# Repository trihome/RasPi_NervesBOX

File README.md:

# Nerves BOX for Raspberry Pi

## はじめに

このボードは、産業用に使用される機器（例：24V駆動のスイッチ、センサー、リレーなど）をRaspberry Piへ接続できるようにします。

詳しくは、Qiitaの記事「[Elixir/NervesでPLC(多機能リレー)を作ってみた](https://qiita.com/myasu/private/a6664d3a3c76503affc7)」をご覧ください。

## 仕様

|機能|仕様|補足|
|:--|:--|:--|
|出力|4ch（フォトリレー絶縁）|シンク（NPN）・ソース（PNP）駆動切り替え可能。各chの動作確認LEDあり。|
|入力|4ch（フォトカプラ絶縁）|〃|
|AD変換|10bit 2ch|非絶縁・入力保護のダイオード付き|
|時刻保持|リアルタイムクロックDS1307|ボタン電池でバックアップ|
|GROVEコネクタ|あり、I2C x 1|5V電源タイプ|
|外部UART端子|あり x 1|RaspberryPiのUARTに直結|
|電源|5V系/24V系は個別に供給|それぞれポリスイッチ（過電流防止）あり|

**J5, J7の接続**

|対応表|GPIO（BCM表記）|本機の端子|
|:--|:--|:--|
|入力|12|X0|
|〃|16|X1|
|〃|20|X2|
|〃|21|X3|
|出力|6|Y0|
|〃|13|Y1|
|〃|19|Y2|
|〃|26|Y3|

**J2の接続**

|駆動したい方法|Pow24+In|Pow24-In||D16|D13||X側COM端子|Y側COM端子|
|:--|:--|:--|:--|:--|:--|:--|:--|:--|
|シンク|+24V|GND|→|点灯|消灯||GND|+24V|
|ソース|GND|+24V|→|消灯|点灯||+24V|GND|

## 作り方

[Manual](doc/README_pcb.jp.md)をご覧ください。

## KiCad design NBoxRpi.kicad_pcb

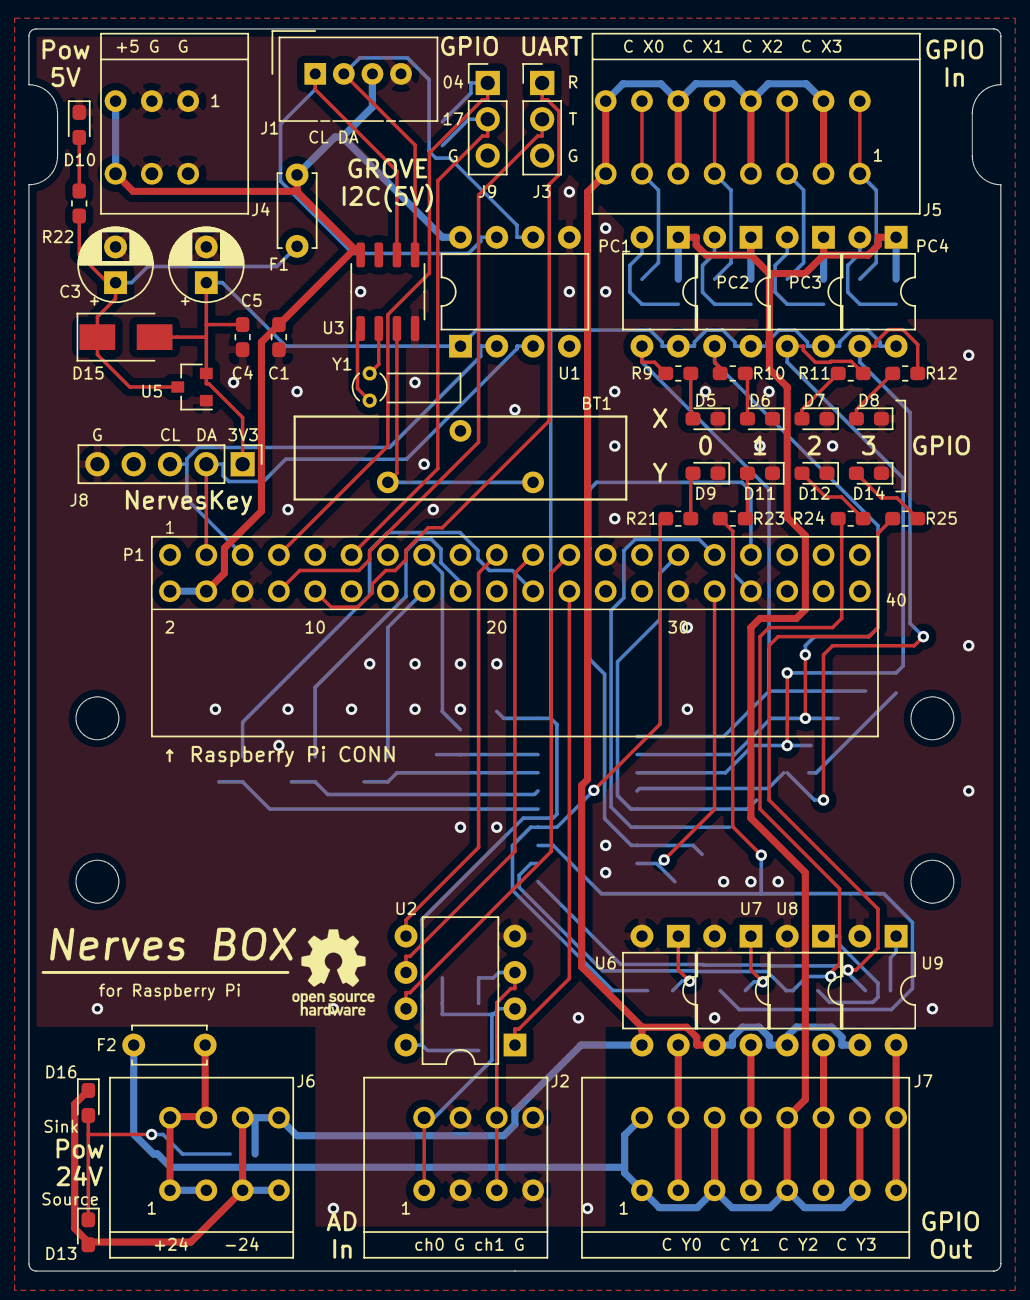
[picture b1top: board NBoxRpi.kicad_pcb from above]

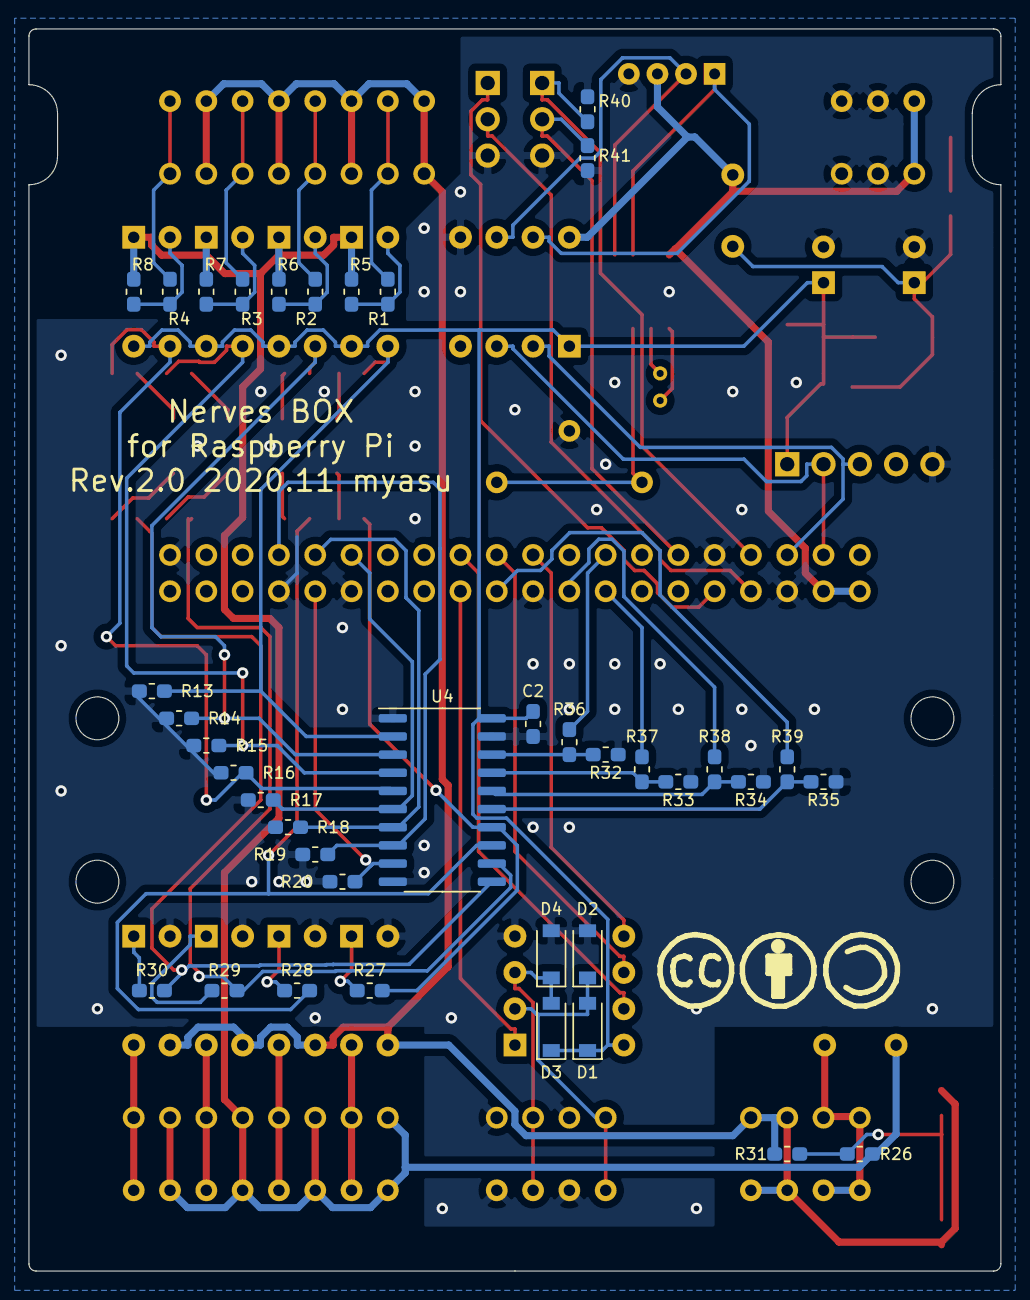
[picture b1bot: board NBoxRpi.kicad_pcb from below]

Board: 2 copper layers, 68.0 x 86.9 mm, 95 parts (38 on the bottom side), 70 nets.

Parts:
BT1: CH243-2032LF; BatteryHolder_Keystone_CH74-2032LF
C1, C2, C4: 0.1uF; C_0603_1608Metric_Pad1.05x0.95mm_HandSolder
C3: 100uF; CP_Radial_D5.0mm_P2.50mm
C5: 220uF; CP_Radial_D5.0mm_P2.50mm
D1, D2, D3, D4: 1N4148W; D_SOD-123
D5, D6, D7, D8: Gr; LED_0603_1608Metric_Pad1.05x0.95mm_HandSolder
D9, D11, D12, D14: Ye; LED_0603_1608Metric_Pad1.05x0.95mm_HandSolder
D10, D13, D16: Red; LED_0603_1608Metric_Pad1.05x0.95mm_HandSolder
D15: SBR1A40SA; D_SMA
F1: 0.17A(MAX0.34); C_Disc_D5.0mm_W2.5mm_P5.00mm
F2: 0.5A(MAX1A); C_Disc_D5.0mm_W2.5mm_P5.00mm
H1: MountingHole; OSHW-Logo_5.7x6mm_SilkScreen
H2: MountingHole; CC-BY-SA
J1: GROVE CONN; NS-Tech_Grove_1x04_P2mm_Vertical
J2, J6: TB401-1-4-E; Terminal_TB401-1-4-E
J3, J9: Pin Header 3; PinHeader_1x03_P2.54mm_Vertical
J4: TB401-1-3-E; Terminal_TB401-1-3-E
J5: TB401-1-8-E; Terminal_TB401-1-8-E
J7: TB401-1-3-E; Terminal_TB401-1-8-E
J8: Pin Header 4; PinHeader_1x05_P2.54mm_Vertical
MH1, MH2, MH3, MH4: MountingHole; MountingHole_3mm
P1: RasPi CONN; Connector_21602X20GRE
PC1, PC2, PC3, PC4: FOD814A300W; DIP-4_W7.62mm
R1, R2, R3, R4, R5, R6, R7, R8, R26, R31: 4.7k; R_0603_1608Metric_Pad1.05x0.95mm_HandSolder
R9, R10, R11, R12, R36, R37, R38, R39: 1k; R_0603_1608Metric_Pad1.05x0.95mm_HandSolder
R13, R14, R15, R16, R17, R18, R19, R20, R32, R33, R34, R35, R40, R41: 10k; R_0603_1608Metric_Pad1.05x0.95mm_HandSolder
R21, R23, R24, R25, R27, R28, R29, R30: 330; R_0603_1608Metric_Pad1.05x0.95mm_HandSolder
R22: 470; R_0603_1608Metric_Pad1.05x0.95mm_HandSolder
U1: AE-PCA9306; DIP-8_W7.62mm
U2: MCP3002; DIP-8_W7.62mm
U3: DS1307+; SO-8_3.9x4.9mm_P1.27mm
U4: 74HC541; SO-20_5.3x12.6mm_P1.27mm
U5: MCP1703AT-3302E; SOT-23
U6, U7, U8, U9: TLP222A; DIP-4_W7.62mm
Y1: 32.768kHz; Crystal_Round_D2.0mm_Vertical

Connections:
+3V3: C2.1, C4.1, C5.1, D1.1, D3.1, D15.2, J8.1, PC1.4, PC2.4, PC3.4, PC4.4, U1.1, U2.8, U4.20, U5.2
+5V: C1.1, F1.2, J1.3, J4.5, J4.6, P1.2, P1.4, U1.8, U3.8
/AD0: D1.2, D2.1, J2.1, J2.2, U2.2
/AD1: D3.2, D4.1, J2.5, J2.6, U2.3
/GPIO2(SDA1): J8.2, P1.3, U1.3
/GPIO3(SCL1): J8.3, P1.5, U1.2
/GPIO4(GCLK): J9.1, P1.7, R40.1
/GPIO5: P1.29, R17.1, U4.6
/GPIO6: P1.31, R18.1, U4.7
/GPIO8(SPI0_CE_N): P1.24, U2.1
/GPIO9(SPI0_MISO): P1.21, U2.6
/GPIO10(SPI0_MOSI): P1.19, U2.5
/GPIO11(SPI0_SCK): P1.23, U2.7
/GPIO12(PWM0): P1.32, R20.1, U4.9
/GPIO13(PWM1): P1.33, R19.1, U4.8
/GPIO14(TXD0): J3.2, P1.8
/GPIO15(RXD0): J3.1, P1.10
/GPIO17(GEN0): J9.2, P1.11, R41.1
/GPIO22(GEN3): P1.15, R36.1
/GPIO23(GEN4): P1.16, R37.1
/GPIO24(GEN5): P1.18, R38.1
/GPIO25(GEN6): P1.22, R39.1
/Pow24+: F2.1, J7.1, J7.2, J7.5, J7.6, J7.9, J7.10, J7.13, J7.14, PC1.1, PC2.1, PC3.1, PC4.1, R5.1, R6.1, R7.1, R8.1, R26.1
/Pow24+In: F2.2, J6.1, J6.2, J6.3, J6.4
/Pow24-: D13.2, D16.1, J5.3, J5.4, J5.7, J5.8, J5.11, J5.12, J5.15, J5.16, J6.5, J6.6, J6.7, J6.8, R31.2, U6.3, U7.3, U8.3, U9.3
/SCL: J1.1, U1.7, U3.6
/SDA: J1.2, U1.6, U3.5
/X00: J5.13, J5.14, R1.2
/X01: J5.9, J5.10, R2.2
/X02: J5.5, J5.6, R3.2
/X03: J5.1, J5.2, R4.2
/Y00: J7.3, J7.4, U6.4
/Y01: J7.7, J7.8, U7.4
/Y02: J7.11, J7.12, U8.4
/Y03: J7.15, J7.16, U9.4
GND: BT1.2, C1.2, C2.2, C3.2, C4.2, C5.2, D2.2, D4.2, D5.1, D6.1, D7.1, D8.1, D9.1, D10.1, D11.1, D12.1, D14.1, J1.4, J2.3, J2.4, J2.7, J2.8, J3.3, J4.1, J4.2, J4.3, J4.4, J8.5, J9.3, P1.6, P1.9, P1.14, P1.20, P1.25, P1.30, P1.34, P1.39, R13.2, R14.2, R15.2, R16.2, R17.2, R18.2, R19.2, R20.2, R32.2, R33.2, R34.2, R35.2, R40.2, R41.2, U1.5, U2.4, U3.4, U4.1, U4.10, U4.19, U5.1, U6.2, U7.2, U8.2, U9.2
unnamed: BT1.1, U3.3
unnamed: C3.1, D15.1, F1.1, R22.1, U5.3
unnamed: D5.2, R9.2
unnamed: D6.2, R10.2
unnamed: D7.2, R11.2
unnamed: D8.2, R12.2
unnamed: D9.2, R21.2
unnamed: D10.2, R22.2
unnamed: D11.2, R23.2
unnamed: D12.2, R24.2
unnamed: D13.1, D16.2, R26.2, R31.1
unnamed: D14.2, R25.2
unnamed: PC1.2, R1.1, R5.2
unnamed: PC1.3, R9.1, R13.1, U4.2
unnamed: PC2.2, R2.1, R6.2
unnamed: PC2.3, R10.1, R14.1, U4.3
unnamed: PC3.2, R3.1, R7.2
unnamed: PC3.3, R11.1, R15.1, U4.4
unnamed: PC4.2, R4.1, R8.2
unnamed: PC4.3, R12.1, R16.1, U4.5
unnamed: R21.1, R27.2, U4.14
unnamed: R23.1, R28.2, U4.13
unnamed: R24.1, R29.2, U4.12
unnamed: R25.1, R30.2, U4.11
unnamed: R27.1, U6.1
unnamed: R28.1, U7.1
unnamed: R29.1, U8.1
unnamed: R30.1, U9.1
unnamed: R32.1, R36.2, U4.18
unnamed: R33.1, R37.2, U4.17
unnamed: R34.1, R38.2, U4.16
unnamed: R35.1, R39.2, U4.15
unnamed: U3.1, Y1.1
unnamed: U3.2, Y1.2

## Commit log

2020-12-07 Add files.

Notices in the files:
parts and their libraries:
Creative Commons Licence
